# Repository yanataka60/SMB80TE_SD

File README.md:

# SHARP SM-B-80TEにSD-Cardとのロード、セーブ機能

　シリアル同期通信によりSM-B-80TEとSD_ACCESS(ARDUINO+SD-CARD)とのロード、セーブを提供するルーチンです。

## 必要なもの
　Z80PIO 1個(標準搭載のZ80PIOとは別のZ80PIOが必要)

　SD_ACCESS基板(「SD_ACCESS」リポジトリ参照)

　2716 1個(MONITOR ROMを差し替えるなら2716 2個)

　ピンヘッダ、フラットケーブル、ブレッドボード・ジャンパーワイヤ等(SD_ACCESS基板の接続方法により適宜用意してください)

## 接続方法
SD_ACCESS(ARDUINO+SD-CARD)と拡張Z80PIOを接続します。拡張Z80PIO外部端子から接続する例を示します。

SD_ACCESS(ARDUINO+SD-CARD)については、「SD_ACCESS」リポジトリを参照してください。

|Arduino(SD_ACCESS)|拡張Z80PIO外部端子(SM-B-80TE)|
| ------------ | ------------ |
|5V|B8　5V|
|GND|B7　GND|
|9(FLG:output)|A4　PORTC BIT1(CHK:input)|
|8(OUT:output)|B4　PORTC BIT0(IN:input)|
|7(CHK:input)|A3　PORTC BIT3(FLG:output)|
|6(IN:input)|B3　PORTC BIT2(OUT:output)|

　今回はTK-85用に用意したSD_ACCESS(ARDUINO+SD-CARD)を流用して繋いでいます。

### SM-B-80TE専用のSD_ACCESS基板を作ってみました。

　基板データは、Kicadフォルダにあります。

#### 部品
|番号|品名|数量|備考|
| ------------ | ------------ | ------------ | ------------ |
|J1|細ピンヘッダ又は基板用リードフレーム|1|秋月電子通商 PHA-1x40SG又はSHP-001|
||J2、J3のいずれか|||
|J2|Micro_SD_Card_Kit|1|秋月電子通商 AE-microSD-LLCNV|
|J3|MicroSD Card Adapter|1|Arduino等に使われる5V電源に対応したもの|
|U2|Arduino_Pro_Mini_5V|1||
||40PinICソケット|1||
|U1|Z80PIO|1|SM-B-80TEに増設済みであれば引き抜いて使用|

.JPG)

.JPG)

## ROMへの書込み
　file_trans_SMB80TE.binを2716に書き込み、SM-B-80TEのIC3 ROMソケットに挿し込みます。

## MONITOR-ROMの差し替え
　SD用LOADルーチン(8800H)、SAVEルーチン(8803H)を直接実行することでSDへのLOAD、SAVEが行えますが、MONITOR-ROMにパッチを当て、SHIFT+A(SD-LOAD)、SHIFT+B(SD-SAVE)で使えるようにすると便利です。

　MONITOR-ROMの内容を読み出し、バイナリエディタ等で以下を修正し、2716に書き込み、MONITOR-ROMと差し替えます。

|ADDRESS(実ADDRESS)|変更前|変更後|
| ------------ | ------------ | ------------ |
|0060(8060)|FE|C3|
|0061(8061)|0C|06|
|0062(8062)|CA|88|

## SD-CARD
　FAT16又はFAT32が認識できます。

## 扱えるファイル
　拡張子btkとなっているバイナリファイルです。

　ファイル名は0000～FFFFまでの16進数4桁を付けてください。(例:1000.btk)

　この16進数4桁がSM-B-80TEからSD-Card内のファイルを識別するファイルNoとなります。

　btkの構造は、バイナリファイル本体データの先頭に開始アドレス、終了アドレスの4Byteのを付加した形になっています。(SAMPLEフォルダの0001.bin、0001.btkを参照)

　パソコンのクロスアセンブラ等でSM-B-80TE用の実行binファイルを作成したらバイナリエディタ等で先頭に開始アドレス、終了アドレスの4Byteを付加し、ファイル名を変更したものをSD-Cardのルートディレクトリに保存すればSM-B-80TEから呼び出せるようになります。

## 操作方法
　異常が無いと思われるのにエラーとなってしまう場合にはSD-CardアダプタのArduinoとSM-B-80TEの両方をリセットしてからやり直してみてください。

### Load
 (直接実行する場合)8800H

 (MONITOR-ROMを差し替えた場合)SHIFT+A

　ADDRESS LEDに「L-F」と表示されるのでファイルNo(xxxx)を16進数4桁で入力してWRキーを押します。

　　　xxxx.BTKをBTKヘッダ情報で示されたアドレスにロードします。ただし、07B0H～07FFHまでの範囲はライトプロテクトされます。

　正常にLoadが完了するとアドレス部にスタートアドレス、データ部にエンドアドレスが表示されます。スタートアドレスが実行開始アドレスであればそのままRUNキーを押すことでプログラムが実行できます。

　「F0F0F0F0F0」と表示された場合はSD-Card未挿入、「F1F1F1F1F1」と表示された場合はファイルNoのファイルが存在しない場合です。確認してください。

### Save
 (直接実行する場合)8803H

 (MONITOR-ROMを差し替えた場合)SHIFT+B

　ADDRESS LEDに「S-F」と表示されるのでファイルNo(xxxx)を16進数4桁で入力してWRキーを押します。

　ADDRESS LEDに「S-S」と表示されるのでSAVEしたい範囲のSTART ADDRESSを16進数4桁で入力してWRキーを押します。

　ADDRESS LEDに「S-E」と表示されるのでSAVEしたい範囲のEND ADDRESSを16進数4桁で入力してWRキーを押します。

　正常にSaveが完了するとアドレス部にスタートアドレス、データ部にエンドアドレスが表示されます。

　「FFFFFFFF」と表示された場合はSD-Card未挿入です。確認してください。

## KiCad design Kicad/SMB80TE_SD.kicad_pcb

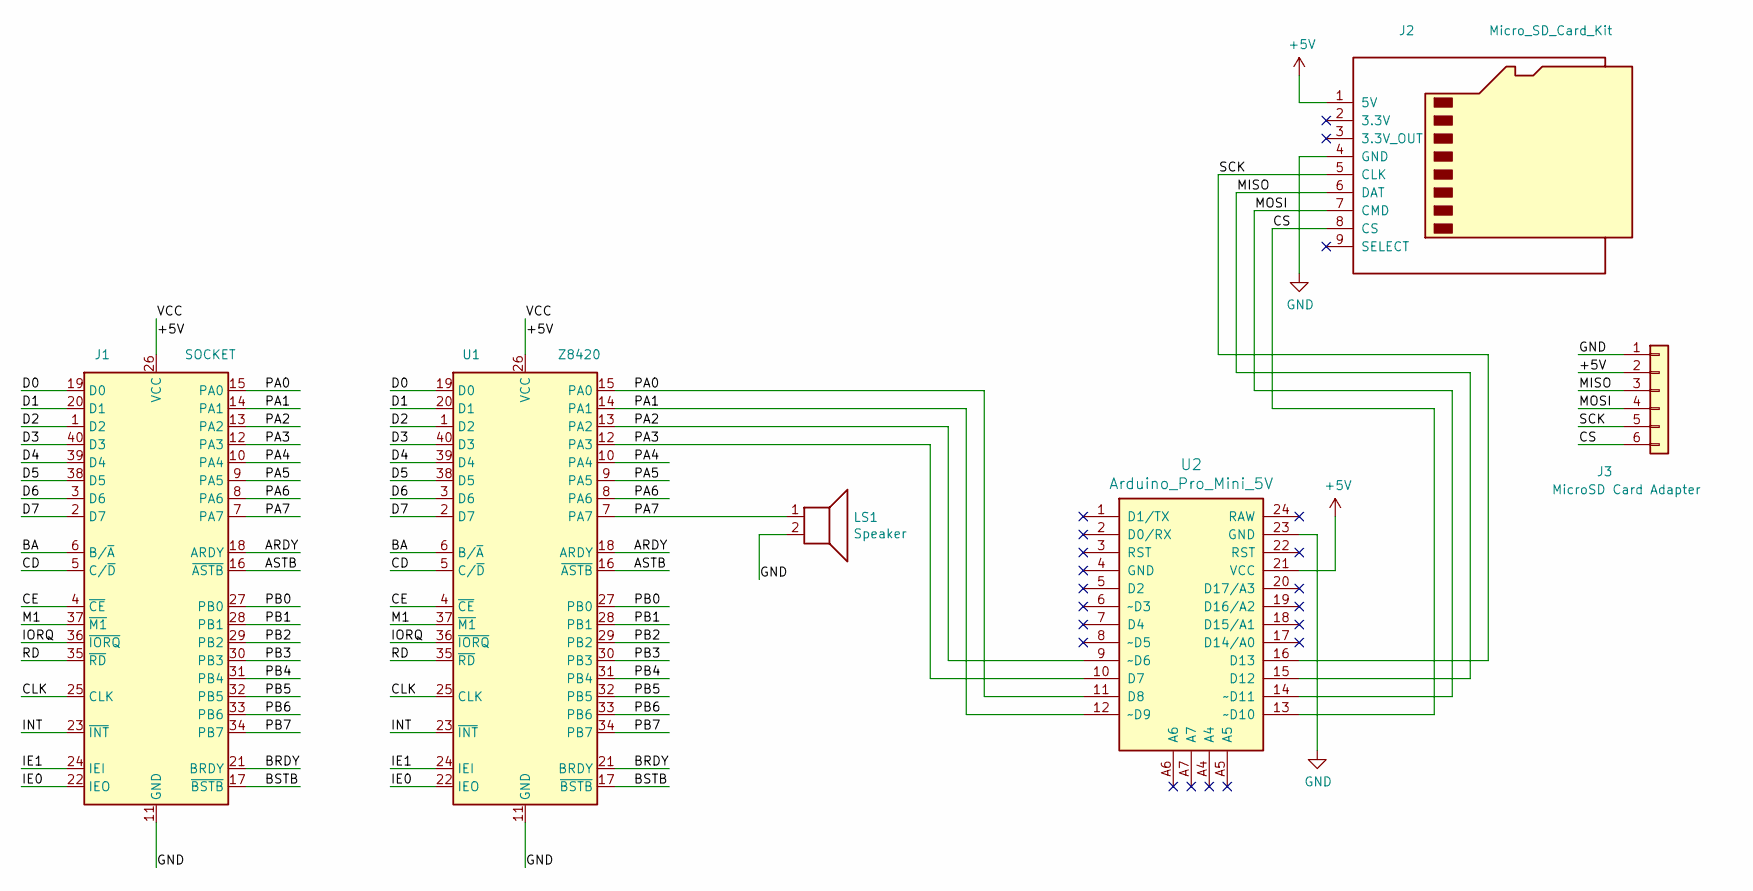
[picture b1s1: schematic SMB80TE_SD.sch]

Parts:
J1: SOCKET; DIP-40_W15.24mm_LongPads
J2: Micro_SD_Card_Kit; AE-microSD-LLCNV
J3: MicroSD Card Adapter; PinSocket_1x06_P2.54mm_Vertical
LS1: Speaker; PinHeader_1x02_P2.54mm_Vertical
U1: Z8420; DIP-40_W15.24mm_LongPads
U2: Arduino_Pro_Mini_5V; Arduino_Pro_Mini

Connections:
+5V: J1.26 (VCC), J2.1 (5V), J3.2, U1.26 (VCC), U2.21 (VCC)
/ARDY: J1.18 (ARDY), U1.18 (ARDY)
/ASTB: J1.16 (~ASTB~), U1.16 (~ASTB~)
/BA: J1.6 (B/~A~), U1.6 (B/~A~)
/BRDY: J1.21 (BRDY), U1.21 (BRDY)
/BSTB: J1.17 (~BSTB~), U1.17 (~BSTB~)
/CD: J1.5 (C/~D~), U1.5 (C/~D~)
/CE: J1.4 (~CE~), U1.4 (~CE~)
/CLK: J1.25 (CLK), U1.25 (CLK)
/CS: J2.8 (CS), J3.6, U2.13 (~~D10)
/D0: J1.19 (D0), U1.19 (D0)
/D1: J1.20 (D1), U1.20 (D1)
/D2: J1.1 (D2), U1.1 (D2)
/D3: J1.40 (D3), U1.40 (D3)
/D4: J1.39 (D4), U1.39 (D4)
/D5: J1.38 (D5), U1.38 (D5)
/D6: J1.3 (D6), U1.3 (D6)
/D7: J1.2 (D7), U1.2 (D7)
/IE0: J1.22 (IEO), U1.22 (IEO)
/IE1: J1.24 (IEI), U1.24 (IEI)
/INT: J1.23 (~INT~), U1.23 (~INT~)
/IORQ: J1.36 (~IORQ~), U1.36 (~IORQ~)
/M1: J1.37 (~M1~), U1.37 (~M1~)
/MISO: J2.6 (DAT), J3.3, U2.15 (D12)
/MOSI: J2.7 (CMD), J3.4, U2.14 (~~D11)
/PA0: J1.15 (PA0), U1.15 (PA0), U2.11 (D8)
/PA1: J1.14 (PA1), U1.14 (PA1), U2.12 (~~D9)
/PA2: J1.13 (PA2), U1.13 (PA2), U2.9 (~~D6)
/PA3: J1.12 (PA3), U1.12 (PA3), U2.10 (D7)
/PA4: J1.10 (PA4), U1.10 (PA4)
/PA5: J1.9 (PA5), U1.9 (PA5)
/PA6: J1.8 (PA6), U1.8 (PA6)
/PA7: J1.7 (PA7), LS1.1, U1.7 (PA7)
/PB0: J1.27 (PB0), U1.27 (PB0)
/PB1: J1.28 (PB1), U1.28 (PB1)
/PB2: J1.29 (PB2), U1.29 (PB2)
/PB3: J1.30 (PB3), U1.30 (PB3)
/PB4: J1.31 (PB4), U1.31 (PB4)
/PB5: J1.32 (PB5), U1.32 (PB5)
/PB6: J1.33 (PB6), U1.33 (PB6)
/PB7: J1.34 (PB7), U1.34 (PB7)
/RD: J1.35 (~RD~), U1.35 (~RD~)
/SCK: J2.5 (CLK), J3.5, U2.16 (D13)
GND: J1.11 (GND), J2.4 (GND), J3.1, LS1.2, U1.11 (GND), U2.23 (GND)

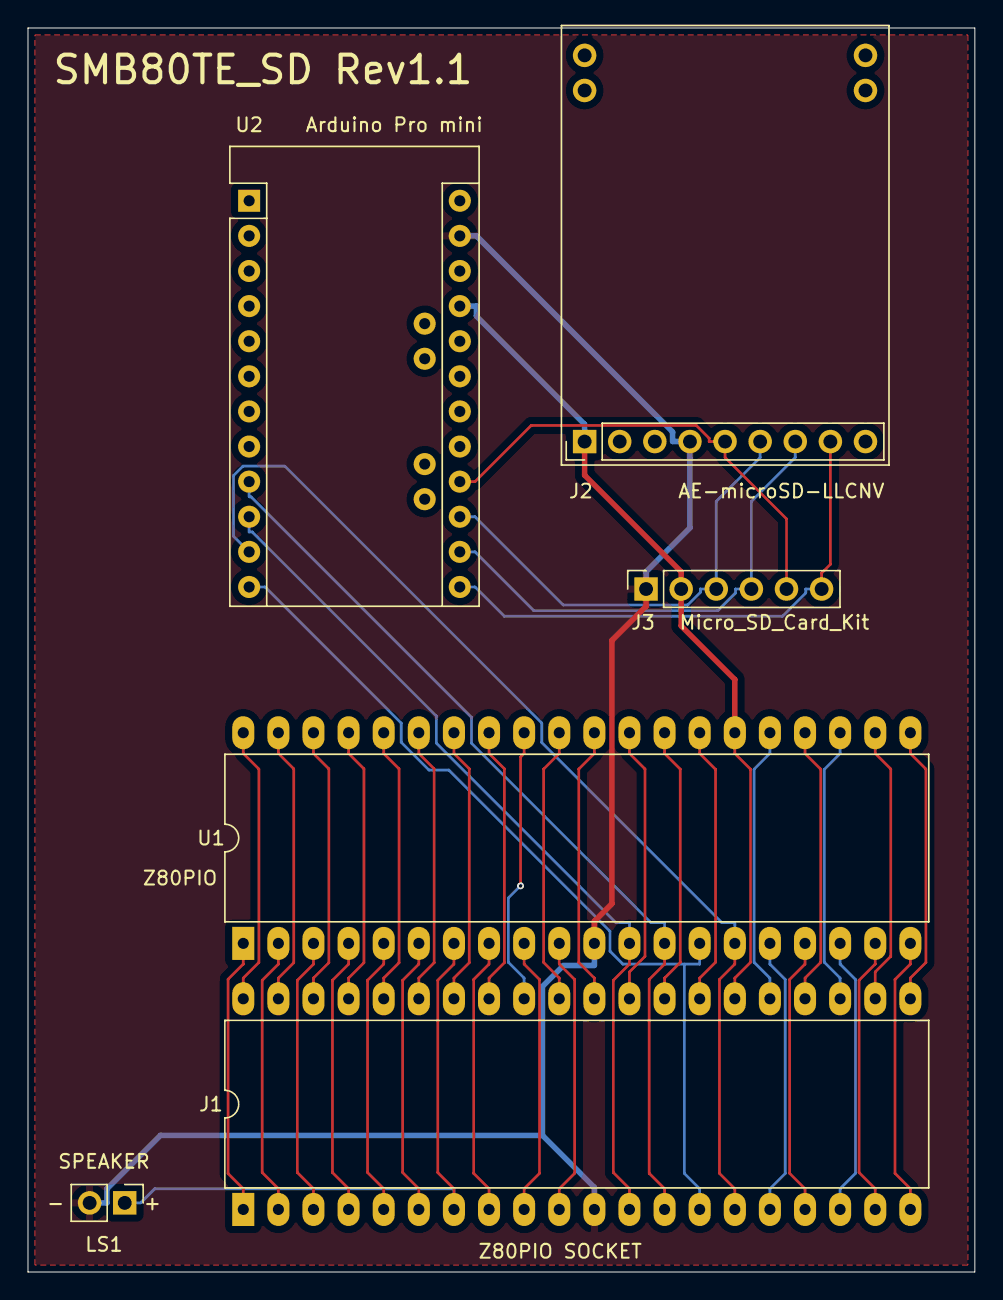
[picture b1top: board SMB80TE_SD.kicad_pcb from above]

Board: 2 copper layers, 68.5 x 90.0 mm, 6 parts (0 on the bottom side), 44 nets.
